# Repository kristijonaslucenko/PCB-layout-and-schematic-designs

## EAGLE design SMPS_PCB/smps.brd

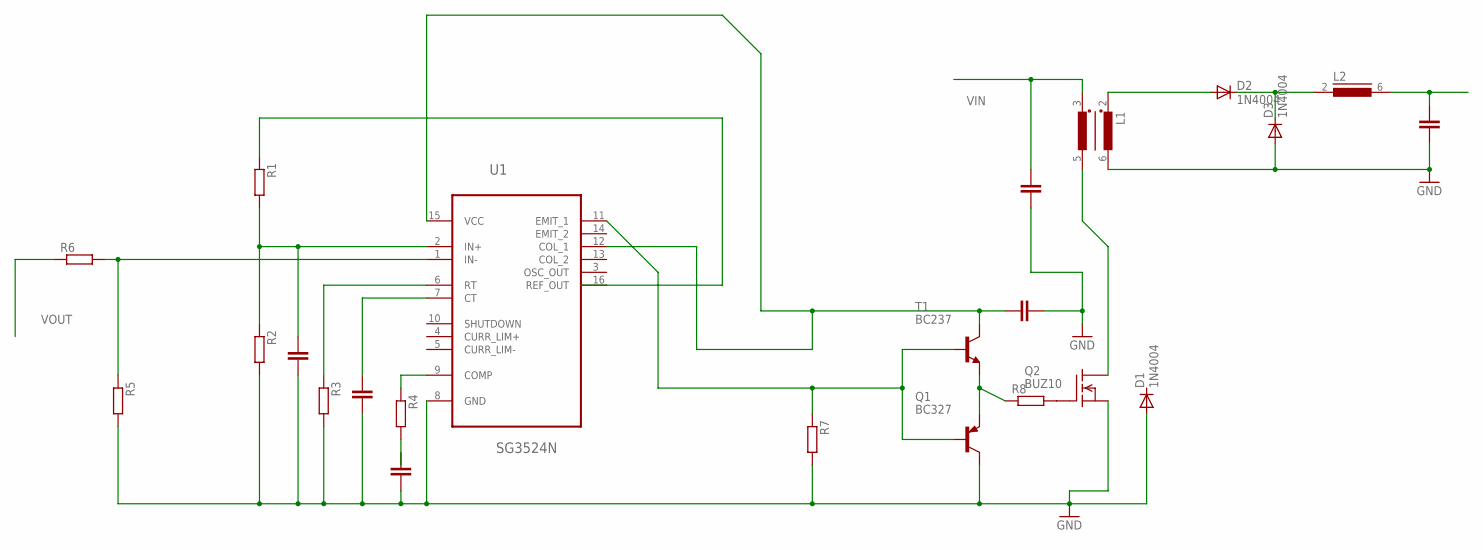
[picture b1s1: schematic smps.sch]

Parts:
D1, D2, D3: 1N4004; DO41-10
L1: RM6-2; RM5-4
L2: RM6; RM6-4
Q1: BC327; TO92
Q2: BUZ10; TO220
R1, R2, R3, R4, R5, R6, R7, R8: R-EU_0204/7; 0204/7
T1: BC237; TO92
U1: SG3524N; DIP254P762X508-16

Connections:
GND: D1.A, D3.A, L1.6 (W1E), Q1.3 (C), Q2.3 (S), R2.2, R3.2, R5.2, R7.2, U1.8 (GND)
unnamed: R1.1, U1.16 (REF_OUT)
unnamed: R1.2, R2.1, U1.2 (IN+)
unnamed: Q1.2 (B), R7.1, T1.2 (B), U1.11 (EMIT_1)
unnamed: T1.3 (C), U1.12 (COL_1), U1.15 (VCC)
unnamed: R3.1, U1.6 (RT)
unnamed: R4.1, U1.9 (COMP)
unnamed: R5.1, R6.2, U1.1 (IN-)
unnamed: Q1.1 (E), R8.1, T1.1 (E)
unnamed: D2.A, L1.2 (W1A)
unnamed: Q2.1 (G), R8.2
unnamed: D2.C, D3.C, L2.2 (1)
unnamed: L1.5 (W2E), Q2.2 (D)
VIN: L1.3 (W2A)
VOUT: L2.6 (2), R6.1

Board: 2 copper layers, 17 parts (0 on the bottom side), 14 nets, no tracks yet.

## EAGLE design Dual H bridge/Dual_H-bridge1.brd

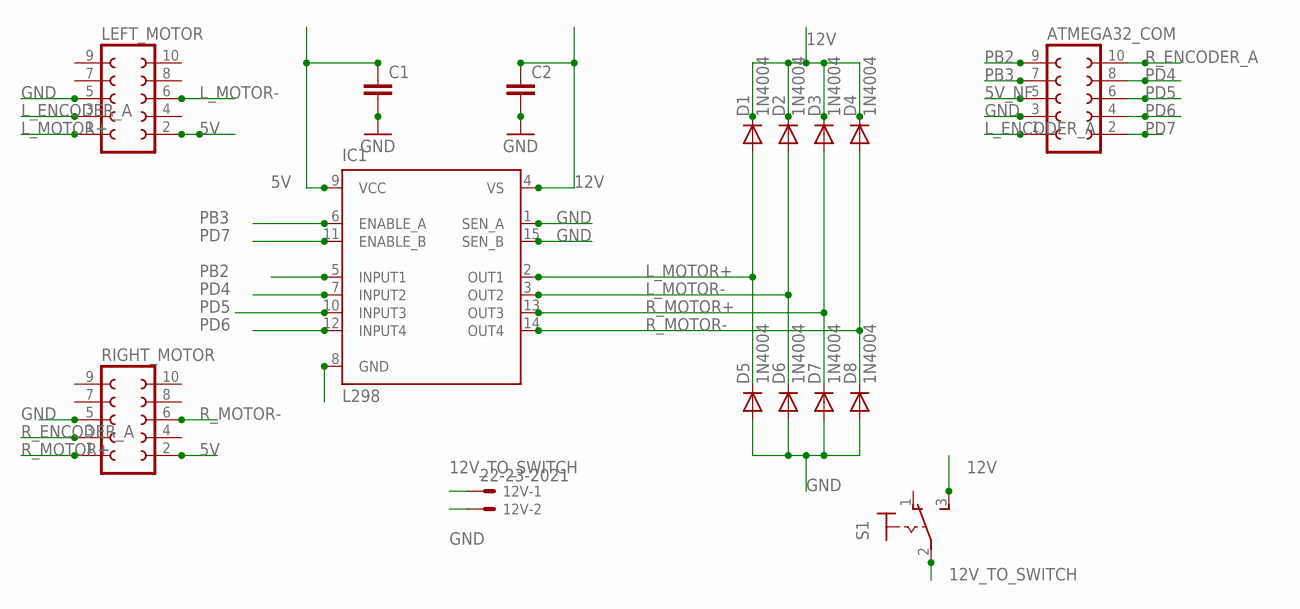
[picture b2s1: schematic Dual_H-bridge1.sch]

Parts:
12V: 22-23-2021
ATMEGA32_COM: FE05-2
C1, C2: C5/3; C5B3
D1, D2, D3, D4, D5, D6, D7, D8: 1N4004; DO41-10
IC1: L298; MULTIWATT-15
LEFT_MOTOR: FE05-2
RIGHT_MOTOR: FE05-2
S1: M9040P

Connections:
5V: C1.1, IC1.9 (VCC), LEFT_MOTOR.2, RIGHT_MOTOR.2
5V_NF: ATMEGA32_COM.5
12V: C2.1, D1.C, D2.C, D3.C, D4.C, IC1.4 (VS), S1.3 (S)
12V_TO_SWITCH: 12V.1, S1.2
GND: 12V.2, ATMEGA32_COM.3, C1.2, C2.2, D5.A, D6.A, D7.A, D8.A, IC1.1 (SEN_A), IC1.8 (GND), IC1.15 (SEN_B), LEFT_MOTOR.5, RIGHT_MOTOR.5
L_ENCODER_A: ATMEGA32_COM.1, LEFT_MOTOR.3
L_MOTOR+: D1.A, D5.C, IC1.2 (OUT1), LEFT_MOTOR.1
L_MOTOR-: D2.A, D6.C, IC1.3 (OUT2), LEFT_MOTOR.6
PB2: ATMEGA32_COM.9, IC1.5 (INPUT1)
PB3: ATMEGA32_COM.7, IC1.6 (ENABLE_A)
PD4: ATMEGA32_COM.8, IC1.7 (INPUT2)
PD5: ATMEGA32_COM.6, IC1.10 (INPUT3)
PD6: ATMEGA32_COM.4, IC1.12 (INPUT4)
PD7: ATMEGA32_COM.2, IC1.11 (ENABLE_B)
R_ENCODER_A: ATMEGA32_COM.10, RIGHT_MOTOR.3
R_MOTOR+: D3.A, D7.C, IC1.13 (OUT3), RIGHT_MOTOR.1
R_MOTOR-: D4.A, D8.C, IC1.14 (OUT4), RIGHT_MOTOR.6

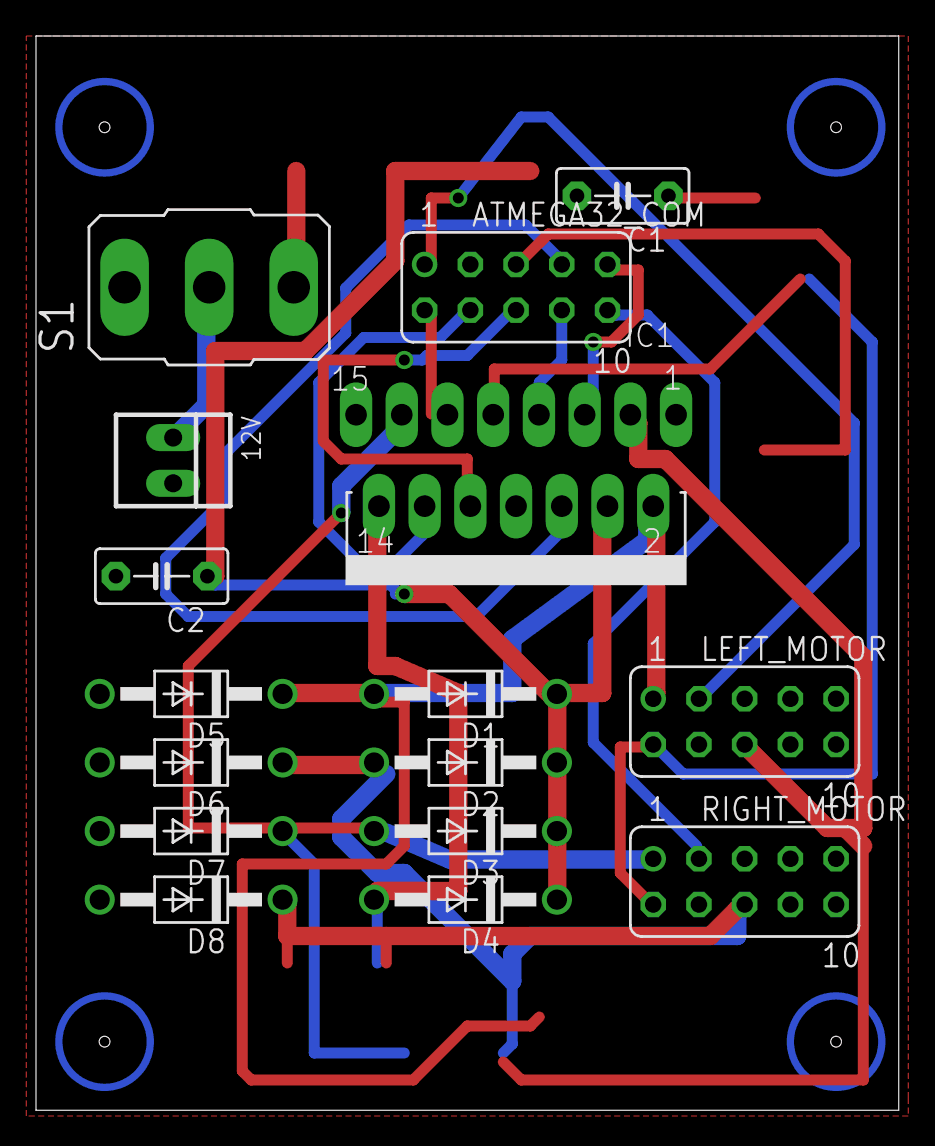
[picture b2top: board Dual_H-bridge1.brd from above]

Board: 2 copper layers, 47.9 x 59.7 mm, 16 parts (0 on the bottom side), 16 nets.

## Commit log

2016-01-12 :space_invader: Added .gitattributes
2016-01-12 Upload
